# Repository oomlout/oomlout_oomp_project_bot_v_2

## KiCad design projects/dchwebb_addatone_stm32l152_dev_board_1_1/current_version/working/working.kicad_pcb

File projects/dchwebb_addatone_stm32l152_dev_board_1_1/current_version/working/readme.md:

# addatone
 
## summary 
* id: dchwebb_addatone_stm32l152_dev_board_1_1
* user: dchwebb
* name: addatone
* board: stm32l152_dev_board_1_1
* repo: https://github.com/dchwebb/Addatone
* src_file_repo_kicad_pcb: Hardware/ARM_Dev_Board/STM32L152_Dev_Board 1.1.kicad_pcb
* src_file_repo_kicad_pcb_link: https://github.com/dchwebb/Addatone/tree/master/Hardware/ARM_Dev_Board/STM32L152_Dev_Board 1.1.kicad_pcb

* src_file_repo_sch: Hardware/AddaTone components.sch
* src_file_repo_sch_link: https://github.com/dchwebb/Addatone/tree/master/Hardware/AddaTone components.sch
* full details link: https://github.com/oomlout/oomlout_oomp_project_bot_v_2/tree/main/projects/dchwebb_addatone_stm32l152_dev_board_1_1/current_version/working

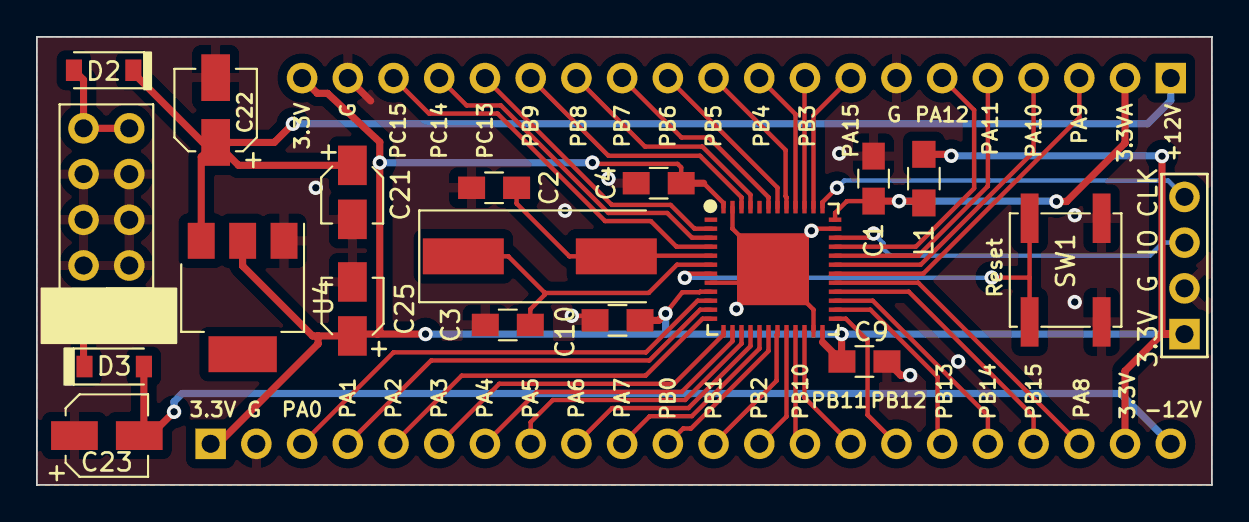
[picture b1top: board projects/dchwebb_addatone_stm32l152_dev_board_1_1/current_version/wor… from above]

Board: 2 copper layers, 65.3 x 24.9 mm, 21 parts (0 on the bottom side), 45 nets.

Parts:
C1, C4, C9, C10: 100nF; C_0805_HandSoldering
C2, C3: 18pF; C_0805_HandSoldering
C21, C25: 10uF; CP_Elec_3x5.3
C22, C23: 22uF; CP_Elec_4x5.8
D2, D3: 1N5819; D_SOD-123
J1: SWD_Header; SWD_header
J2: Conn_01x20_Female; Pin_Header_Straight_1x20_Pitch2.54mm
J3: Conn_01x22_Female; Pin_Header_Straight_1x22_Pitch2.54mm
J4: Eurorack_10_pin_power; Pin_Header_Straight_2x05_Pitch2.54mm
L1: L; R_0805_HandSoldering
SW1: SW_Push; SW_SPST_EVPBF
U1: STM32L451CCUx; ARM-UQFN-48-7x7mm_Pitch0.5mm
U4: LM1117-3.3; SOT-223
Y1: Crystal; Crystal_SMD

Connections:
+3.3VA: C1.1, J2.2, L1.1, U1.36
+3V3: C4.1, C9.1, C10.1, C25.1, J1.1, J2.20, J3.1, J3.21, L1.2, U1.9, U1.24, U1.48, U4.2
+12V: D2.2, J4.9, J4.10
-12V: D3.1, J4.1, J4.2
GND: C1.2, C2.2, C3.2, C4.2, C9.2, C10.2, C21.2, C22.2, C23.1, C25.2, J1.2, J2.7, J2.19, J3.2, J4.3, J4.4, J4.5, J4.6, J4.7, J4.8, SW1.1, U1.8, U1.23, U1.35, U1.47, U1.49, U4.1
unnamed: C2.1, U1.5, Y1.2
unnamed: C3.1, U1.6, Y1.1
PA0: J3.3, U1.10
PA1: J3.4, U1.11
PA2: J3.5, U1.12
PA3: J3.6, U1.13
PA4: J3.7, U1.14
PA5: J3.8, U1.15
PA6: J3.9, U1.16
PA7: J3.10, U1.17
PA8: J3.20, U1.29
PA9: J2.3, U1.30
PA10: J2.4, U1.31
PA11: J2.5, U1.32
PA12: J2.6, U1.33
PA15: J2.8, U1.38
PB0: J3.11, U1.18
PB1: J3.12, U1.19
PB2: J3.13, U1.20
PB3: J2.9, U1.39
PB4: J2.10, U1.40
PB5: J2.11, U1.41
PB6: J2.12, U1.42
PB7: J2.13, U1.43
PB8: J2.14, U1.45
PB9: J2.15, U1.46
PB10: J3.14, U1.21
PB11: J3.15, U1.22
PB12: J3.16, U1.25
PB13: J3.17, U1.26
PB14: J3.18, U1.27
PB15: J3.19, U1.28
PC13: J2.16, U1.2
PC14: J2.17, U1.3
PC15: J2.18, U1.4
Reset: SW1.2, U1.7
SWCLK: J1.4, U1.37
SWDIO: J1.3, U1.34
VCC: C21.1, C22.1, D2.1, J2.1, U4.3
VEE: C23.2, D3.2, J3.22

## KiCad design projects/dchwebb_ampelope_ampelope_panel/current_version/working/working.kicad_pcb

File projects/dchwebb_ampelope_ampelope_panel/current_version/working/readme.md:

# ampelope
 
## summary 
* id: dchwebb_ampelope_ampelope_panel
* user: dchwebb
* name: ampelope
* board: ampelope_panel
* repo: https://github.com/dchwebb/Ampelope
* src_file_repo_kicad_pcb: Hardware/Ampelope_Adapter.kicad_pcb
* src_file_repo_kicad_pcb_link: https://github.com/dchwebb/Ampelope/tree/main/Hardware/Ampelope_Adapter.kicad_pcb
* src_file_repo_kicad_sch: Hardware/Ampelope_Adapter.kicad_sch
* src_file_repo_kicad_sch_link: https://github.com/dchwebb/Ampelope/tree/main/Hardware/Ampelope_Adapter.kicad_sch

* src_file_repo_sch: 
* src_file_repo_sch_link: https://github.com/dchwebb/Ampelope/tree/main/
* full details link: https://github.com/oomlout/oomlout_oomp_project_bot_v_2/tree/main/projects/dchwebb_ampelope_ampelope_panel/current_version/working

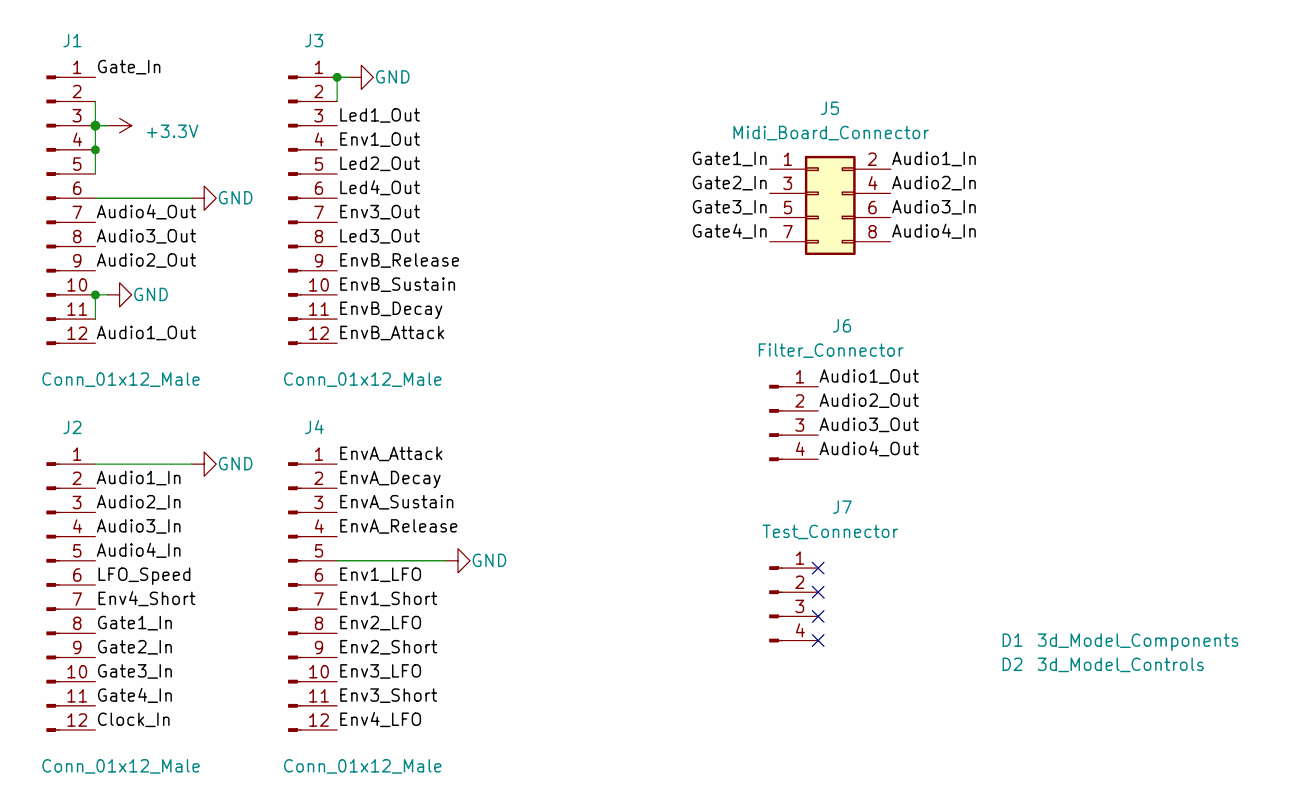
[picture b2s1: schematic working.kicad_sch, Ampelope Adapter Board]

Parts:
D1: 3d_Model_Components; 3D_Dummy
D2: 3d_Model_Controls; 3D_Dummy
J1, J2, J3, J4: Conn_01x12_Male; PinSocket_1x12_P2.54mm_Vertical
J5: Midi_Board_Connector; PinHeader_2x04_P2.54mm_Vertical
J6: Filter_Connector; PinHeader_1x04_P2.54mm_Vertical
J7: Test_Connector; PinHeader_1x04_P2.54mm_Vertical

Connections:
+3V3: J1.2, J1.3, J1.4, J1.5
/Audio1_In: J2.2, J5.2
/Audio1_Out: J1.12, J6.1
/Audio2_In: J2.3, J5.4
/Audio2_Out: J1.9, J6.2
/Audio3_In: J2.4, J5.6
/Audio3_Out: J1.8, J6.3
/Audio4_In: J2.5, J5.8
/Audio4_Out: J1.7, J6.4
/Clock_In: J2.12
/Env1_LFO: J4.6
/Env1_Out: J3.4
/Env1_Short: J4.7
/Env2_LFO: J4.8
/Env2_Short: J4.9
/Env3_LFO: J4.10
/Env3_Out: J3.7
/Env3_Short: J4.11
/Env4_LFO: J4.12
/Env4_Short: J2.7
/EnvA_Attack: J4.1
/EnvA_Decay: J4.2
/EnvA_Release: J4.4
/EnvA_Sustain: J4.3
/EnvB_Attack: J3.12
/EnvB_Decay: J3.11
/EnvB_Release: J3.9
/EnvB_Sustain: J3.10
/Gate1_In: J2.8, J5.1
/Gate2_In: J2.9, J5.3
/Gate3_In: J2.10, J5.5
/Gate4_In: J2.11, J5.7
/Gate_In: J1.1
/LFO_Speed: J2.6
/Led1_Out: J3.3
/Led2_Out: J3.5
/Led3_Out: J3.8
/Led4_Out: J3.6
GND: J1.6, J1.10, J1.11, J2.1, J3.1, J3.2, J4.5

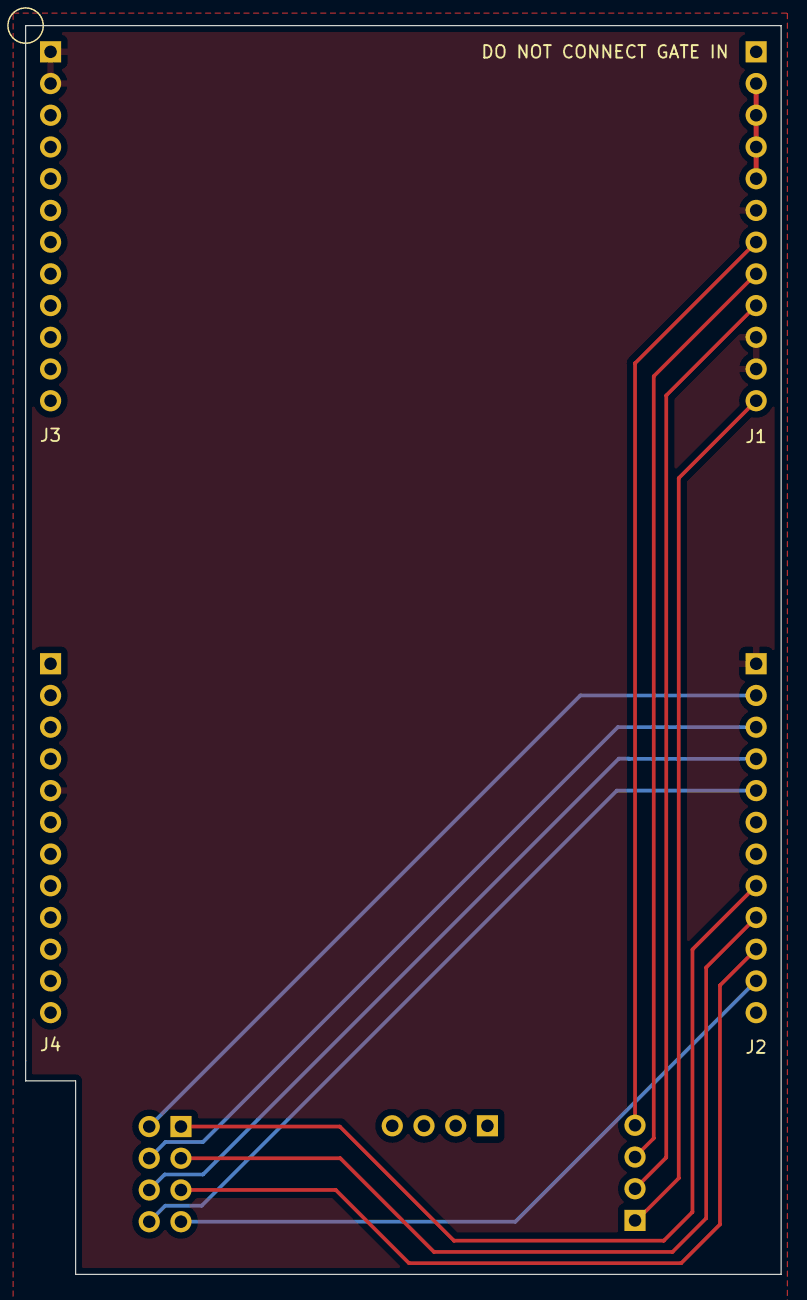
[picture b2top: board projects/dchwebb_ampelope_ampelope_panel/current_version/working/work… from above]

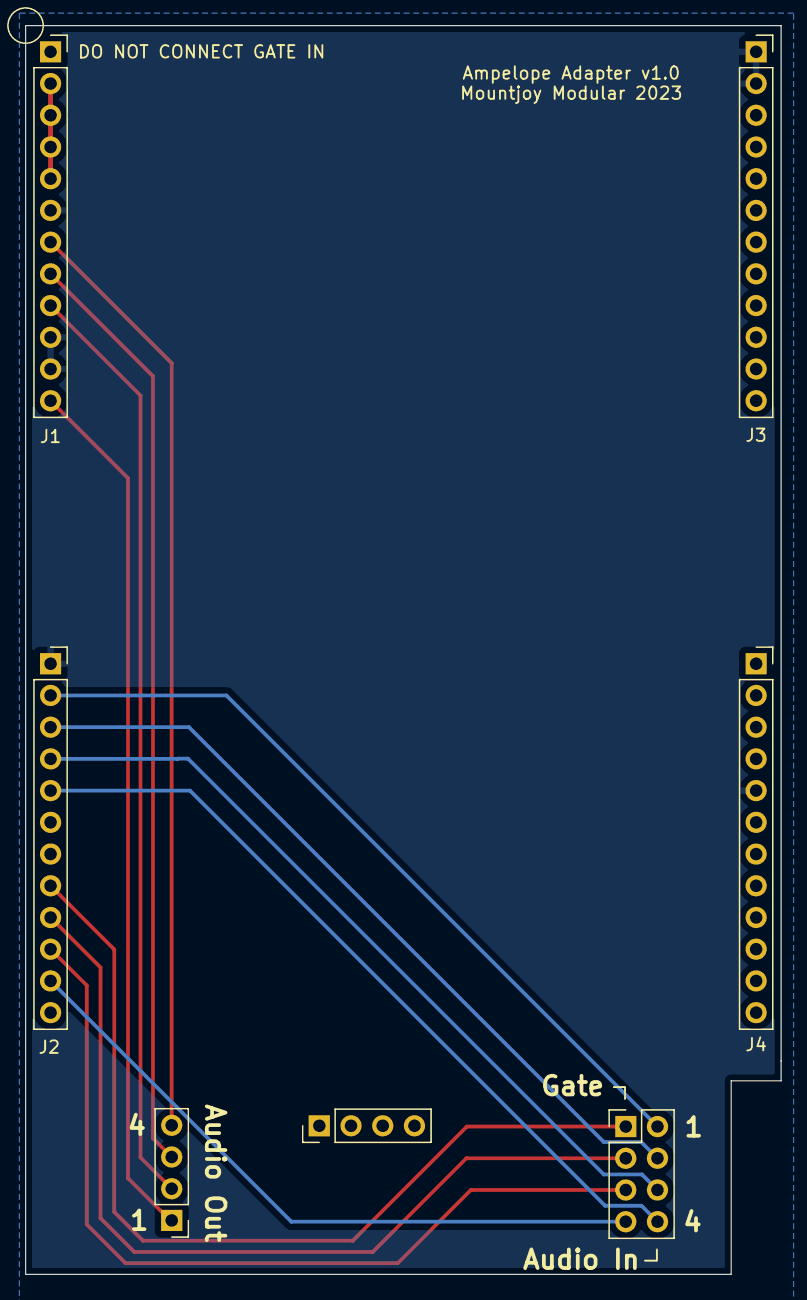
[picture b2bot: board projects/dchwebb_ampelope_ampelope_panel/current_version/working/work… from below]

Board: 2 copper layers, 60.5 x 100.0 mm, 9 parts (8 on the bottom side), 14 nets.

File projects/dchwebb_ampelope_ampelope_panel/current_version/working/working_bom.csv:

"Id";"Designator";"Footprint";"Quantity";"Designation";"Supplier and ref";
1;"D2";"3D_Dummy";1;"3d_Model_Controls";;;
2;"J2,J4,J1,J3";"PinSocket_1x12_P2.54mm_Vertical";4;"Conn_01x12_Male";;;
3;"J6";"PinHeader_1x04_P2.54mm_Vertical";1;"Filter_Connector";;;
4;"D1";"3D_Dummy";1;"3d_Model_Components";;;
5;"J5";"PinHeader_2x04_P2.54mm_Vertical";1;"Midi_Board_Connector";;;
6;"J7";"PinHeader_1x04_P2.54mm_Vertical";1;"Test_Connector";;;

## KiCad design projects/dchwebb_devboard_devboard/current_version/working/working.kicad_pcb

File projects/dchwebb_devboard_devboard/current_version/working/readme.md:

# devboard
 
## summary 
* id: dchwebb_devboard_devboard
* user: dchwebb
* name: devboard
* board: devboard
* repo: https://github.com/dchwebb/DevBoard
* src_file_repo_kicad_pcb: bu/DevBoard.kicad_pcb
* src_file_repo_kicad_pcb_link: https://github.com/dchwebb/DevBoard/tree/master/bu/DevBoard.kicad_pcb
* src_file_repo_kicad_sch: Base_Controls.kicad_sch
* src_file_repo_kicad_sch_link: https://github.com/dchwebb/DevBoard/tree/master/Base_Controls.kicad_sch

* src_file_repo_sch: bu/DevBoard.sch
* src_file_repo_sch_link: https://github.com/dchwebb/DevBoard/tree/master/bu/DevBoard.sch
* full details link: https://github.com/oomlout/oomlout_oomp_project_bot_v_2/tree/main/projects/dchwebb_devboard_devboard/current_version/working

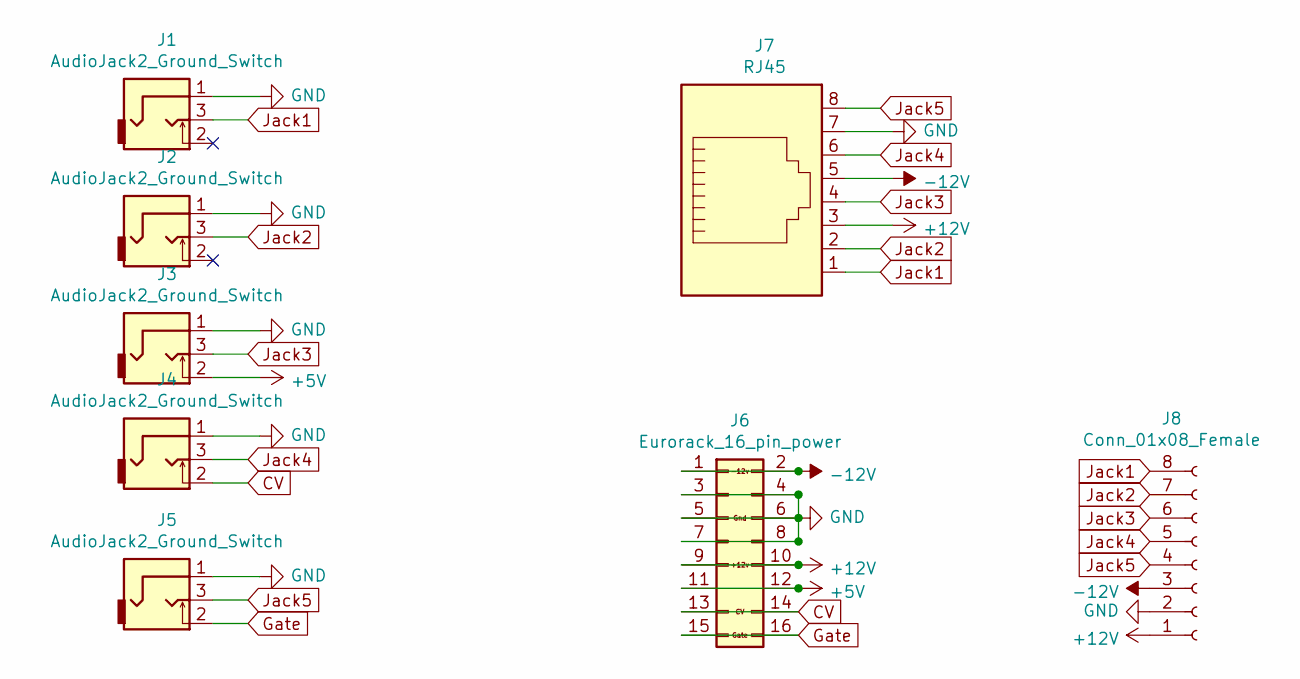
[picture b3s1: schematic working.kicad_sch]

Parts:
J1, J2, J3, J4, J5: AudioJack2_Ground_Switch; THONKICONN_hole
J6: Eurorack_16_pin_power; Eurorack_16_pin_header
J7: RJ45; RJ45_8
J8: Conn_01x08_Female; Pin_Header_Straight_1x08_Pitch2.54mm

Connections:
+5V: J3.2, J6.11, J6.12
+12V: J6.9, J6.10, J7.3, J8.1
-12V: J6.1, J6.2, J7.5, J8.3
CV: J4.2, J6.13, J6.14
GND: J1.1, J2.1, J3.1, J4.1, J5.1, J6.3, J6.4, J6.5, J6.6, J6.7, J6.8, J7.7, J8.2
Gate: J5.2, J6.15, J6.16
Jack1: J1.3, J7.1, J8.8
Jack2: J2.3, J7.2, J8.7
Jack3: J3.3, J7.4, J8.6
Jack4: J4.3, J7.6, J8.5
Jack5: J5.3, J7.8, J8.4

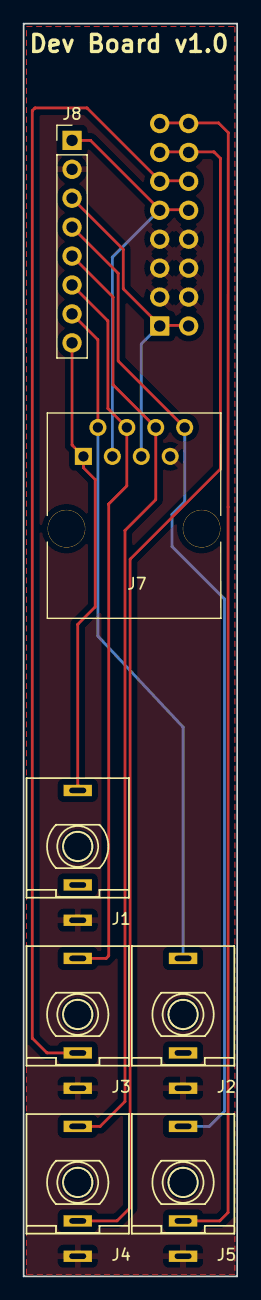
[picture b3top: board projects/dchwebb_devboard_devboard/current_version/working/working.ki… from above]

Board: 2 copper layers, 18.8 x 110.0 mm, 8 parts (1 on the bottom side), 11 nets.

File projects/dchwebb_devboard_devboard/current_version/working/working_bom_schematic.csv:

"Source:","C:\gh\oomlout_oomp_project_bot_v_2\projects\dchwebb_devboard_devboard\current_version\working\working.kicad_sch"
"Date:","30/09/2023 02:53:22"
"Tool:","Eeschema 7.0.6"
"Generator:","C:/Program Files/KiCad/7.0/bin/scripting/plugins/bom_csv_grouped_by_value_with_fp.py"
"Component Count:","8"
"Ref","Qnty","Value","Cmp name","Footprint","Description","Vendor","DNP"
"J1, J2, J3, J4, J5","5","AudioJack2_Ground_Switch","AudioJack2_Ground_Switch-thonkiconn","PlayDice:THONKICONN_hole","","",""
"J6","1","Eurorack_16_pin_power","Eurorack_16_pin_power-Eurorack_Header","PlayDice:Eurorack_16_pin_header","","",""
"J7","1","RJ45","RJ45","Connectors:RJ45_8","RJ connector, 8P8C (8 positions 8 connected)","",""
"J8","1","Conn_01x08_Female","Conn_01x08_Female-Connector","Pin_Headers:Pin_Header_Straight_1x08_Pitch2.54mm","","",""

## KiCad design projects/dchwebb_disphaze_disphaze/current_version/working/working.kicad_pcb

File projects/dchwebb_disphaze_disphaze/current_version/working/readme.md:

# disphaze
 
## summary 
* id: dchwebb_disphaze_disphaze
* user: dchwebb
* name: disphaze
* board: disphaze
* repo: https://github.com/dchwebb/DisPhaze
* src_file_repo_kicad_pcb: Hardware/bu/DisPhaze.kicad_pcb
* src_file_repo_kicad_pcb_link: https://github.com/dchwebb/DisPhaze/tree/master/Hardware/bu/DisPhaze.kicad_pcb
* src_file_repo_kicad_sch: Hardware/DisPhaze.kicad_sch
* src_file_repo_kicad_sch_link: https://github.com/dchwebb/DisPhaze/tree/master/Hardware/DisPhaze.kicad_sch

* src_file_repo_sch: Hardware/DisPhaze.sch
* src_file_repo_sch_link: https://github.com/dchwebb/DisPhaze/tree/master/Hardware/DisPhaze.sch
* full details link: https://github.com/oomlout/oomlout_oomp_project_bot_v_2/tree/main/projects/dchwebb_disphaze_disphaze/current_version/working

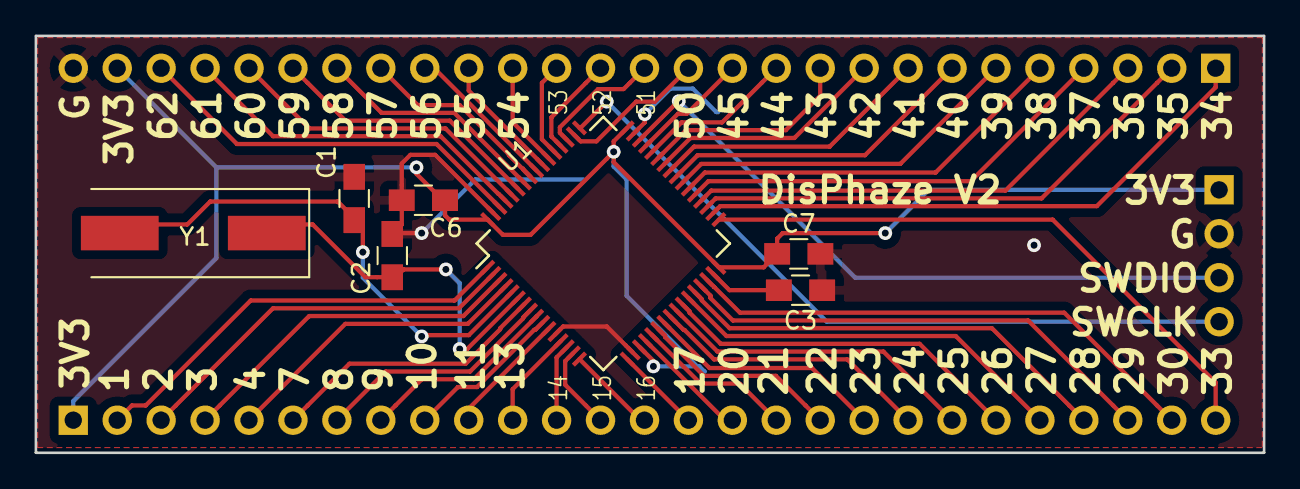
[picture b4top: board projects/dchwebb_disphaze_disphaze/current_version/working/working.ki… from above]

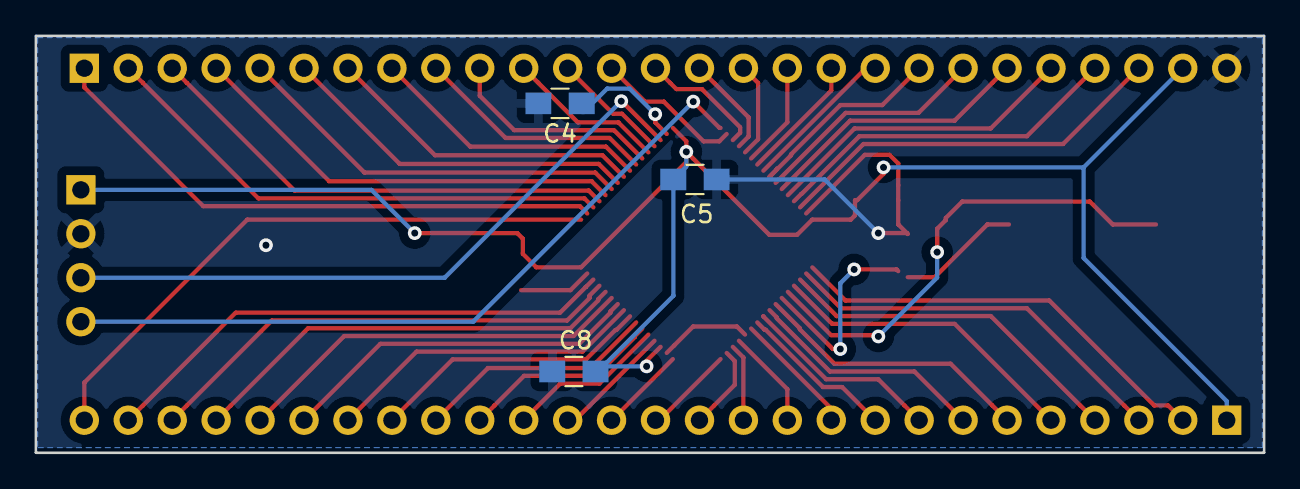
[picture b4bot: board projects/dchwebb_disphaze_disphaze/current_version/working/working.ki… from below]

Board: 2 copper layers, 71.0 x 24.1 mm, 13 parts (3 on the bottom side), 59 nets.

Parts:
C1, C2: 18pF; C_0805_HandSoldering
C3, C4: 2.2uF; C_0805_HandSoldering
C5, C6, C7, C8: 100nF; C_0805_HandSoldering
J1, J2: Conn_01x27; Connector_27x2.54mm
J3: Conn_01x04_Male; 4pin_header
U1: STM32F405RGTx; LQFP-64_10x10mm_P0.5mm
Y1: Crystal; Crystal_SMD_HC49-SD

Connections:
+3V3: C5.1, C6.1, C7.1, C8.1, J1.1, J2.26, J3.1, U1.19, U1.32, U1.48, U1.64
GND: C1.2, C2.2, C3.1, C4.2, C5.2, C6.2, C7.2, C8.2, J2.27, J3.2, U1.12, U1.18, U1.63
unnamed: C1.1, U1.5, Y1.2
unnamed: C2.1, U1.6, Y1.1
unnamed: C3.2, U1.31
unnamed: C4.1, U1.47
SWCLK: J3.4, U1.49
SWDIO: J3.3, U1.46
p1: J1.2, U1.1
p2: J1.3, U1.2
p3: J1.4, U1.3
p4: J1.5, U1.4
p7: J1.6, U1.7
p8: J1.7, U1.8
p9: J1.8, U1.9
p10: J1.9, U1.10
p11: J1.10, U1.11
p13: J1.11, U1.13
p14: J1.12, U1.14
p15: J1.13, U1.15
p16: J1.14, U1.16
p17: J1.15, U1.17
p20: J1.16, U1.20
p21: J1.17, U1.21
p22: J1.18, U1.22
p23: J1.19, U1.23
p24: J1.20, U1.24
p25: J1.21, U1.25
p26: J1.22, U1.26
p27: J1.23, U1.27
p28: J1.24, U1.28
p29: J1.25, U1.29
p30: J1.26, U1.30
p33: J1.27, U1.33
p34: J2.1, U1.34
p35: J2.2, U1.35
p36: J2.3, U1.36
p37: J2.4, U1.37
p38: J2.5, U1.38
p39: J2.6, U1.39
p40: J2.7, U1.40
p41: J2.8, U1.41
p42: J2.9, U1.42
p43: J2.10, U1.43
p44: J2.11, U1.44
p45: J2.12, U1.45
p50: J2.13, U1.50
p51: J2.14, U1.51
p52: J2.15, U1.52
p53: J2.16, U1.53
p54: J2.17, U1.54
p55: J2.18, U1.55
p56: J2.19, U1.56
p57: J2.20, U1.57
p58: J2.21, U1.58
p59: J2.22, U1.59
p60: J2.23, U1.60
p61: J2.24, U1.61
p62: J2.25, U1.62

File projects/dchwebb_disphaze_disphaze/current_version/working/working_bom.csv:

"Id";"Designator";"Footprint";"Quantity";"Designation";"Supplier and ref";
1;"C3,C4";"C_0805_HandSoldering";2;"2.2uF";;;
2;"C6,C7,C8,C5";"C_0805_HandSoldering";4;"100nF";;;
3;"J2,J1";"Connector_27x2.54mm";2;"Conn_01x27";;;
4;"J3";"4pin_header";1;"Conn_01x04_Male";;;
5;"U1";"LQFP-64_10x10mm_P0.5mm";1;"STM32F405RGTx";;;
6;"C1,C2";"C_0805_HandSoldering";2;"18pF";;;
7;"Y1";"Crystal_SMD_HC49-SD";1;"Crystal";;;

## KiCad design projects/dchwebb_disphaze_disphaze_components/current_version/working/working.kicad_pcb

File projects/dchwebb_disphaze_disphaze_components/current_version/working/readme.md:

# disphaze
 
## summary 
* id: dchwebb_disphaze_disphaze_components
* user: dchwebb
* name: disphaze
* board: disphaze_components
* repo: https://github.com/dchwebb/DisPhaze
* src_file_repo_kicad_pcb: Hardware_v3/DisPhaze_Components.kicad_pcb
* src_file_repo_kicad_pcb_link: https://github.com/dchwebb/DisPhaze/tree/master/Hardware_v3/DisPhaze_Components.kicad_pcb
* src_file_repo_kicad_sch: Hardware_v3/DisPhaze_Components.kicad_sch
* src_file_repo_kicad_sch_link: https://github.com/dchwebb/DisPhaze/tree/master/Hardware_v3/DisPhaze_Components.kicad_sch

* src_file_repo_sch: Hardware/DisPhaze.sch
* src_file_repo_sch_link: https://github.com/dchwebb/DisPhaze/tree/master/Hardware/DisPhaze.sch
* full details link: https://github.com/oomlout/oomlout_oomp_project_bot_v_2/tree/main/projects/dchwebb_disphaze_disphaze_components/current_version/working

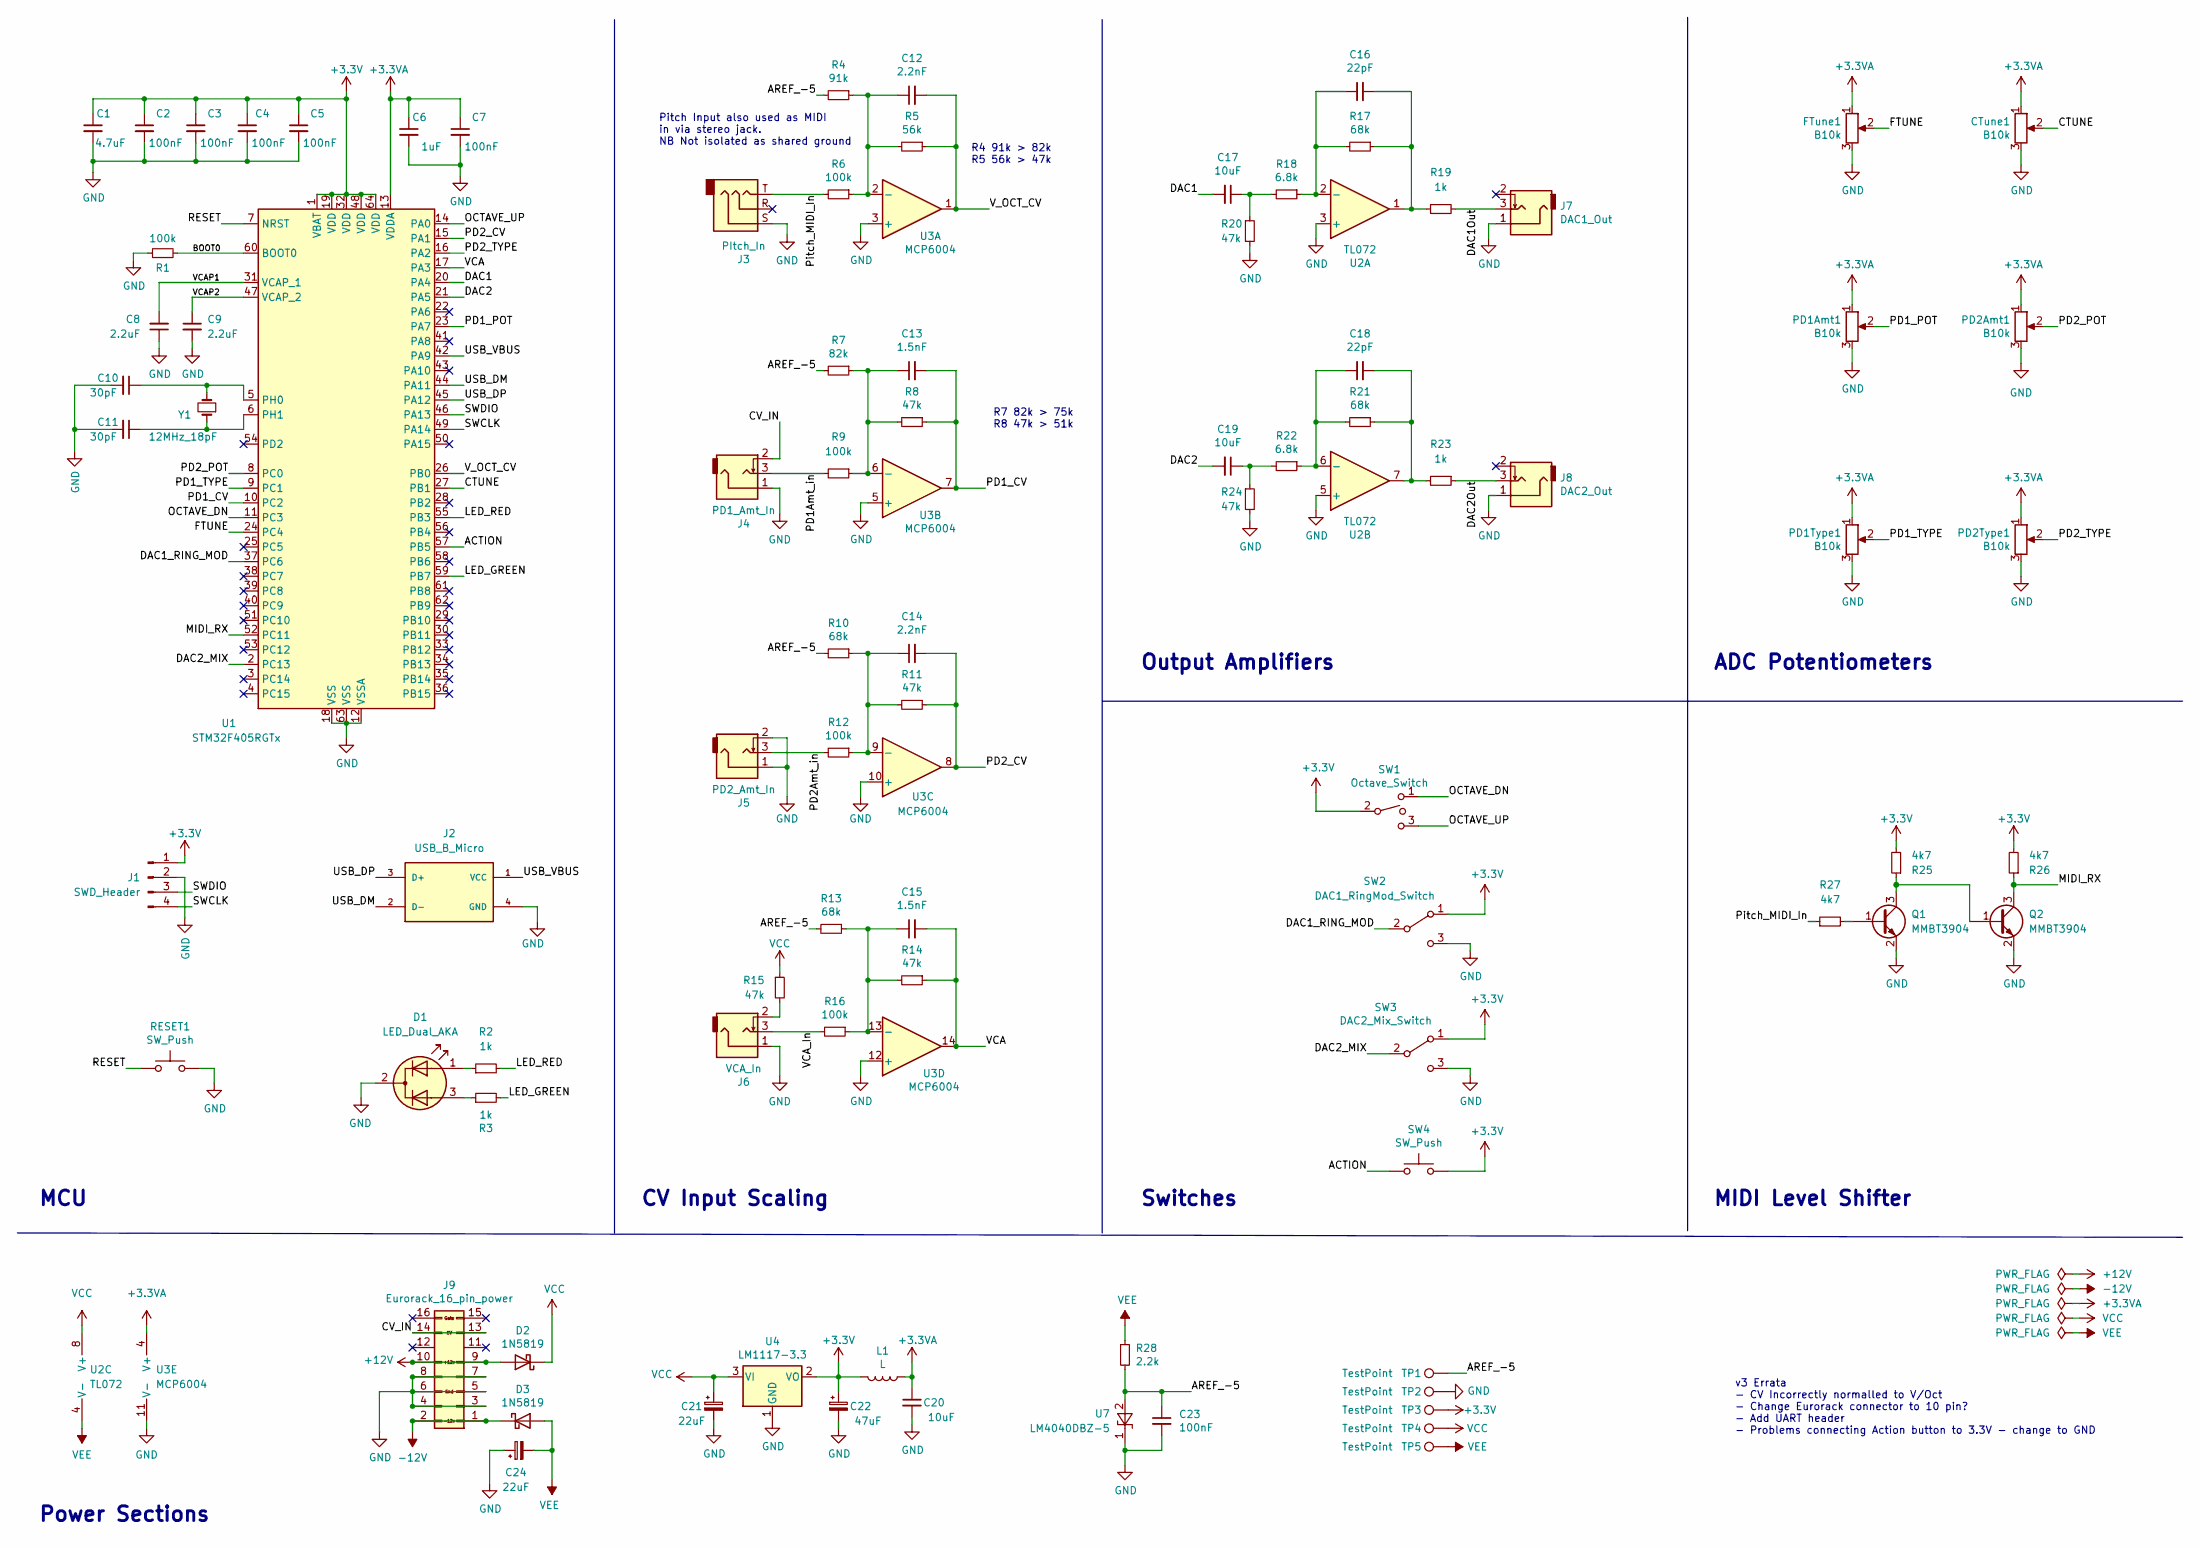
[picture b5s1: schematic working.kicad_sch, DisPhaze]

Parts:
C1: 4.7uF; C_0603_1608Metric
C2, C3, C4, C5, C7, C23: 100nF; C_0603_1608Metric
C6: 1uF; C_0603_1608Metric
C8, C9: 2.2uF; C_0603_1608Metric
C10, C11: 30pF; C_0603_1608Metric
C12, C14: 2.2nF; C_0603_1608Metric
C13, C15: 1.5nF; C_0603_1608Metric
C16, C18: 22pF; C_0603_1608Metric
C17, C19: 10uF; C_0603_1608Metric
C20: 10uF; C_0805_2012Metric
C21, C24: 22uF; CP_Elec_4x5.3
C22: 47uF; CP_Elec_5x5.4
CTune1: B10k; Alpha_9mm_Potentiometer_Aligned
D1: LED_Dual_AKA; LED_D3.0mm-3
D2, D3: 1N5819; D_SOD-123
FTune1: B10k; Alpha_9mm_Potentiometer_Aligned
J1: SWD_Header; SWD_header
J2: USB_B_Micro; USB_TE_1734517-1
J3: PItch_In; Thonkiconn_Stereo-PJ366ST
J4: PD1_Amt_In; THONKICONN_hole
J5: PD2_Amt_In; THONKICONN_hole
J6: VCA_In; THONKICONN_hole
J7: DAC1_Out; THONKICONN_hole
J8: DAC2_Out; THONKICONN_hole
J9: Eurorack_16_pin_power; Eurorack_16_pin_header
L1: L; L_0805_2012Metric
PD1Amt1, PD1Type1, PD2Amt1, PD2Type1: B10k; Alpha_9mm_Potentiometer_Aligned
Q1, Q2: MMBT3904; SOT-23; Part_Number C20526
R1: 100k; R_0603_1608Metric; Part_Number C25803
R2, R3, R19, R23: 1k; R_0603_1608Metric
R4: 91k; R_0603_1608Metric
R5: 56k; R_0603_1608Metric
R6, R9, R12, R16: 100k; R_0603_1608Metric
R7: 82k; R_0603_1608Metric
R8, R11, R14, R15, R20, R24: 47k; R_0603_1608Metric
R10, R13, R17, R21: 68k; R_0603_1608Metric
R18, R22: 6.8k; R_0603_1608Metric
R25, R26, R27: 4k7; R_0603_1608Metric; Part_Number C23162
R28: 2.2k; R_0603_1608Metric
RESET1: SW_Push; SW_SPST_EVQQ2
SW1: Octave_Switch; SPDTSubMiniature
SW2: DAC1_RingMod_Switch; SPDTSubMiniature
SW3: DAC2_Mix_Switch; SPDTSubMiniature
SW4: SW_Push; SW_PUSH_6mm_aligned
TP1, TP2, TP3, TP4, TP5: TestPoint; 1.3mm_Test_Point
U1: STM32F405RGTx; LQFP-64_10x10mm_P0.5mm
U2: TL072; SOIC-8_3.9x4.9mm_P1.27mm
U3: MCP6004; SOIC-14_3.9x8.7mm_P1.27mm
U4: LM1117-3.3; SOT-223-3_TabPin2
U7: LM4040DBZ-5; SOT-23
Y1: 12MHz_18pF; Crystal_SMD_0603-2Pin_6.0x3.5mm

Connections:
+3.3VA: C6.1, C7.1, C20.1, CTune1.1, FTune1.1, L1.1, PD1Amt1.1, PD1Type1.1, PD2Amt1.1, PD2Type1.1, U1.13 (VDDA), U3.4 (V+)
+3V3: C1.1, C2.1, C3.1, C4.1, C5.1, C22.1, J1.1, L1.2, R25.2, R26.2, SW1.2, SW2.1 (A), SW3.1 (A), SW4.2, TP3.1, U1.1 (VBAT), U1.19 (VDD), U1.32 (VDD), U1.48 (VDD), U1.64 (VDD), U4.2 (VO)
+12V: D2.2 (A), J9.9, J9.10
-12V: D3.1 (K), J9.1, J9.2
/ACTION: SW4.1, U1.57 (PB5)
/AREF_-5: C23.1, R4.2, R7.2, R10.2, R13.2, R28.2, TP1.1, U7.2 (A)
/BOOT0: R1.2, U1.60 (BOOT0)
/CTUNE: CTune1.2, U1.27 (PB1)
/CV_IN: J4.2, J9.13, J9.14
/DAC1: C17.2, U1.20 (PA4)
/DAC1Out: J7.3, R19.2
/DAC1_RING_MOD: SW2.2 (B), U1.37 (PC6)
/DAC2: C19.2, U1.21 (PA5)
/DAC2Out: J8.3, R23.1
/DAC2_MIX: SW3.2 (B), U1.2 (PC13)
/FTUNE: FTune1.2, U1.24 (PC4)
/LED_GREEN: R3.2, U1.59 (PB7)
/LED_RED: R2.2, U1.55 (PB3)
/MIDI_RX: Q2.3 (C), R26.1, U1.52 (PC11)
/OCTAVE_DN: SW1.1, U1.11 (PC3)
/OCTAVE_UP: SW1.3, U1.14 (PA0)
/PD1Amt_in: J4.3, R9.2
/PD1_CV: C13.2, R8.1, U1.10 (PC2), U3.7
/PD1_POT: PD1Amt1.2, U1.23 (PA7)
/PD1_TYPE: PD1Type1.2, U1.9 (PC1)
/PD2Amt_in: J5.3, R12.2
/PD2_CV: C14.2, R11.1, U1.15 (PA1), U3.8
/PD2_POT: PD2Amt1.2, U1.8 (PC0)
/PD2_TYPE: PD2Type1.2, U1.16 (PA2)
/Pitch_MIDI_In: J3.T, R6.2, R27.1
/RESET: RESET1.1, U1.7 (NRST)
/SWCLK: J1.4, U1.49 (PA14)
/SWDIO: J1.3, U1.46 (PA13)
/USB_DM: J2.2 (D-), U1.44 (PA11)
/USB_DP: J2.3 (D+), U1.45 (PA12)
/USB_VBUS: J2.1 (VCC), U1.42 (PA9)
/VCA: C15.2, R14.1, U1.17 (PA3), U3.14
/VCAP1: C8.2, U1.31 (VCAP_1)
/VCAP2: C9.1, U1.47 (VCAP_2)
/VCA_In: J6.3, R16.2
/V_OCT_CV: C12.2, R5.1, U1.26 (PB0), U3.1
GND: C1.2, C2.2, C3.2, C4.2, C5.2, C6.2, C7.2, C8.1, C9.2, C10.2, C11.2, C20.2, C21.2, C22.2, C23.2, C24.1, CTune1.3, D1.2 (K), FTune1.3, J1.2, J2.4 (GND), J3.S, J4.1, J5.1, J5.2, J6.1, J7.1, J8.1, J9.3, J9.4, J9.5, J9.6, J9.7, J9.8, PD1Amt1.3, PD1Type1.3, PD2Amt1.3, PD2Type1.3, Q1.2 (E), Q2.2 (E), R1.1, R20.2, R24.2, RESET1.2, SW2.3 (C), SW3.3 (C), TP2.1, U1.12 (VSSA), U1.18 (VSS), U1.63 (VSS), U2.3 (+), U2.5 (+), U3.3 (+), U3.5 (+), U3.10 (+), U3.11 (V-), U3.12 (+), U4.1 (GND), U7.1 (K)
unnamed: C10.1, U1.5 (PH0), Y1.2
unnamed: C11.1, U1.6 (PH1), Y1.1
unnamed: C12.1, R4.1, R5.2, R6.1, U3.2 (-)
unnamed: C13.1, R7.1, R8.2, R9.1, U3.6 (-)
unnamed: C14.1, R10.1, R11.2, R12.1, U3.9 (-)
unnamed: C15.1, R13.1, R14.2, R16.1, U3.13 (-)
unnamed: C16.1, R17.2, R18.1, U2.2 (-)
unnamed: C16.2, R17.1, R19.1, U2.1
unnamed: C17.1, R18.2, R20.1
unnamed: C18.1, R21.2, R22.1, U2.6 (-)
unnamed: C18.2, R21.1, R23.2, U2.7
unnamed: C19.1, R22.2, R24.1
unnamed: D1.1 (A1), R2.1
unnamed: D1.3 (A2), R3.1
unnamed: J6.2, R15.2
unnamed: Q1.1 (B), R27.2
unnamed: Q1.3 (C), Q2.1 (B), R25.1
VCC: C21.1, D2.1 (K), R15.1, TP4.1, U2.8 (V+), U4.3 (VI)
VEE: C24.2, D3.2 (A), R28.1, TP5.1, U2.4 (V-)

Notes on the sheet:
CV Input Scaling
v3 Errata - CV Incorrectly normalled to V/Oct - Change Eurorack connector to 10 pin? - Add UART header - Problems connecting Action button to 3.3V - change to GND
Output Amplifiers
ADC Potentiometers
Pitch Input also used as MIDI in via stereo jack. NB Not isolated as shared ground
MCU
R7 82k > 75k R8 47k > 51k
Power Sections
Switches
R4 91k > 82k R5 56k > 47k
MIDI Level Shifter
